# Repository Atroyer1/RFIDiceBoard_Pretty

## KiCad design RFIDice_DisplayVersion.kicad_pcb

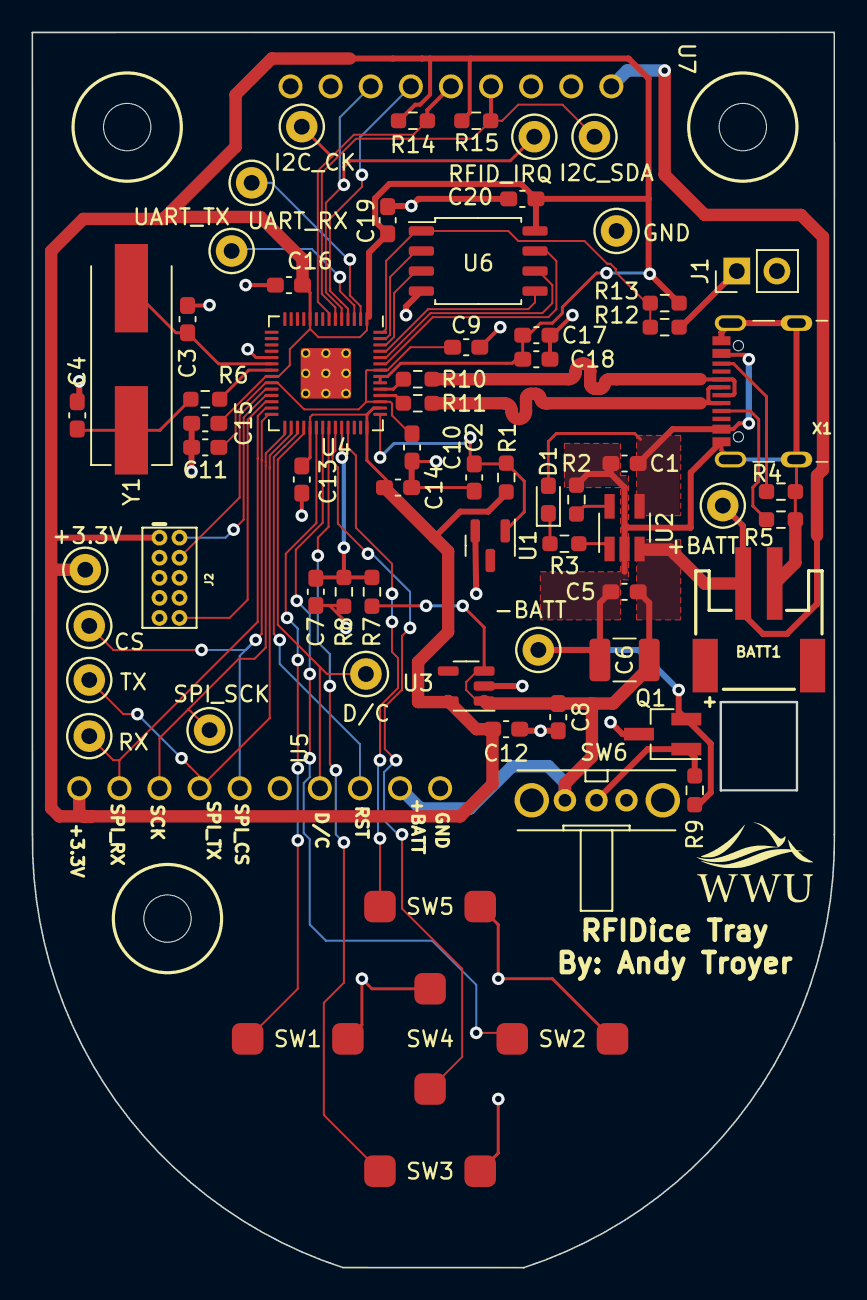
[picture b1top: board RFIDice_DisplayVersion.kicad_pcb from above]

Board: 2 copper layers, 50.8 x 78.3 mm, 73 parts (0 on the bottom side), 48 nets.

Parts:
 : LOGO
+3.3V: TestPoint; TestPoint_Keystone_5000-5004_Miniature
+BATT: TestPoint; TestPoint_Keystone_5000-5004_Miniature
-BATT: TestPoint; TestPoint_Keystone_5000-5004_Miniature
BATT1: Battery_Cell; JSTPH2
C1, C5: 4.7µF; C_0603_1608Metric_Pad1.08x0.95mm_HandSolder
C2, C7: 0.1µF; C_0603_1608Metric_Pad1.08x0.95mm_HandSolder
C3, C4: 27pF; C_0603_1608Metric_Pad1.08x0.95mm_HandSolder
C6: 22mF; C_1210_3225Metric_Pad1.33x2.70mm_HandSolder
C8, C12: 10µF; C_0603_1608Metric_Pad1.08x0.95mm_HandSolder
C9, C11, C13, C14, C15, C16, C17, C18, C19, C20: 100nF; C_0603_1608Metric_Pad1.08x0.95mm_HandSolder
C10: 1µF; C_0603_1608Metric_Pad1.08x0.95mm_HandSolder
CS: TestPoint; TestPoint_Keystone_5000-5004_Miniature
D1: LED; LED_0603_1608Metric_Pad1.05x0.95mm_HandSolder
D/C: TestPoint; TestPoint_Keystone_5000-5004_Miniature
GND: TestPoint; TestPoint_Keystone_5000-5004_Miniature
I2C_CK, I2C_SDA: TestPoint; TestPoint_Keystone_5000-5004_Miniature
J1: Conn_01x02; PinHeader_1x02_P2.54mm_Vertical
J2: CORTEX_JTAG_DEBUG_MINIMUM_PTH; 2X5-PTH-1.27MM
Q1: Q_NMOS_DGS; SOT-23_Handsoldering
R1, R6, R12: 1kΩ; R_0603_1608Metric_Pad0.98x0.95mm_HandSolder
R2, R7, R8, R14, R15: 10kΩ; R_0603_1608Metric_Pad0.98x0.95mm_HandSolder
R3: 470Ω; R_0603_1608Metric_Pad0.98x0.95mm_HandSolder
R4, R5: 5.1kΩ; R_0603_1608Metric_Pad0.98x0.95mm_HandSolder
R9: 470kΩ; R_0603_1608Metric_Pad0.98x0.95mm_HandSolder
R10, R11: 27Ω; R_0603_1608Metric_Pad0.98x0.95mm_HandSolder
R13: DNF; R_0603_1608Metric_Pad0.98x0.95mm_HandSolder
RFID_IRQ: TestPoint; TestPoint_Keystone_5000-5004_Miniature
RX: TestPoint; TestPoint_Keystone_5000-5004_Miniature
SPI_SCK: TestPoint; TestPoint_Keystone_5000-5004_Miniature
SW1, SW2, SW3, SW4, SW5: SW_Push; EVP-ASDC1A_Tactile_PushButton
SW6: OS102011MA1Q
TX: TestPoint; TestPoint_Keystone_5000-5004_Miniature
U1: LM4040DBZ-3; SOT-23
U2: MCP73831T-2ACI/OT; SOT-23-5_HandSoldering
U3: MIC5219-3.3YM5; SOT-23-5
U4: RP2040; RP2040-QFN-56
U5: Display; ThroughHoldDisplayMount
U6: W25Q128JVS; SOIC-8_5.23x5.23mm_P1.27mm
U7: PN532; ThroughHolePN532BrkOutBoardMount
U$6, U$6#2, U$6#3: MOUNTINGHOLE_3.0
UART_RX: TestPoint; TestPoint_Keystone_5000-5004_Miniature
UART_TX: TestPoint; TestPoint_Keystone_5000-5004_Miniature
X1: USB_C; USB_C_CUSB31-CFM2AX-01-X_copy
Y1: ABLS-12.000MHZ-B4-T; Crystal_SMD_HC49-US

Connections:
+1V1: C9.1, C10.1, C11.1, U4.23 (DVDD), U4.45 (VREG_VOUT), U4.50 (DVDD)
+3V3: +3.3V.1, C12.1, C13.1, C14.1, C15.1, C16.1, C17.1, C18.1, C19.1, C20.1, J2.1 (VCC), R1.1, R13.1, R14.2, R15.2, U3.5 (OUT), U4.1 (IOVDD), U4.10 (IOVDD), U4.22 (IOVDD), U4.33 (IOVDD), U4.42 (IOVDD), U4.44 (VREG_IN), U4.48 (USB_VDD), U4.49 (IOVDD), U5.1 (Lite), U6.8 (VCC)
+5V: C1.1, D1.2 (A), U2.4 (VDD), X1.A4B9 (VBUS), X1.B4A9 (VBUS)
+BATT: +BATT.1, BATT1.1 (+), C5.1, C6.1, C8.1, R7.1, SW6.1, U2.3 (VBAT), U3.1 (IN), U3.3 (EN), U5.9 (VCC), U7.1 (3.3V)
-BATT: -BATT.1, BATT1.2 (-), C1.2, C5.2, C6.2, Q1.3 (S), R2.2, R4.1, R5.1, R9.2, U2.2 (VSS), X1.A1B12 (GND), X1.B1A12 (GND), X1.M1, X1.M2, X1.M3, X1.M4
/2USB_D+: R10.1, U4.47 (USB_DP)
/2USB_D-: R11.1, U4.46 (USB_DM)
/ADC_VRef: C2.1, R1.2, U1.1 (K), U4.43 (ADC_AVDD)
/BTN1: SW1.1, U4.34 (GPIO22)
/BTN2: SW2.1, U4.35 (GPIO23)
/BTN3: SW3.1, U4.36 (GPIO24)
/BTN4: SW4.1, U4.37 (GPIO25)
/BTN5: SW5.1, U4.39 (GPIO27_ADC1)
/DISP_DATA/COMMAND: D/C.1, U4.32 (GPIO21), U5.7 (D/C)
/DISP_RST: U4.31 (GPIO20), U5.8 (Reset)
/HALF_BATT_REF: C7.1, R7.2, R8.1, U4.38 (GPIO26_ADC0)
/I2C0_SCL: I2C_CK.1, R14.1, U4.7 (GPIO5), U7.5 (SSEL/SCL/RX)
/I2C0_SDA: I2C_SDA.1, R15.1, U4.6 (GPIO4), U7.4 (MOSI/SDA/TX)
/PN532_IRQ: RFID_IRQ.1, U4.5 (GPIO3), U7.7 (IRQ)
/PN532_RSTOUT_N: U4.4 (GPIO2), U7.6 (RSTOUT_N)
/QSPI_SCLK: U4.52 (QSPI_SCLK), U6.6 (CLK)
/QSPI_SS: R12.2, R13.2, U4.56 (QSPI_SS), U6.1 (~CS)
/QSPL_SD0: U4.53 (QSPI_SD0), U6.5 (DI(IO0))
/QSPL_SD1: U4.55 (QSPI_SD1), U6.2 (DO(IO1))
/QSPL_SD2: U4.54 (QSPI_SD2), U6.3 (IO2)
/QSPL_SD3: U4.51 (QSPI_SD3), U6.7 (IO3)
/SPI_CS: CS.1, U4.28 (GPIO17), U5.5 (TFT_CS)
/SPI_RX: RX.1, U4.27 (GPIO16), U5.2 (MISO)
/SPI_SCK: SPI_SCK.1, U4.29 (GPIO18), U5.3 (SCK)
/SPI_TX: TX.1, U4.30 (GPIO19), U5.4 (MOSI)
/SWCLK: J2.4 (SWDCLK), U4.24 (SWCLK)
/SWD: J2.2 (SWDIO), U4.25 (SWD)
/UART0_RX: U4.2 (GPIO0), UART_RX.1
/UART0_TX: U4.3 (GPIO1), UART_TX.1
/USB_D+: R10.2, X1.A6 (D+), X1.B6 (D+)
/USB_D-: R11.2, X1.A7 (D-), X1.B7 (D-)
/XIN: C3.2, U4.20 (XIN), Y1.2
/XOUT: R6.2, U4.21 (XOUT)
/~RESET: J2.10 (~RESET), U4.26 (RUN)
/~USB_BOOT: J1.1, R12.1
GND: C2.2, C3.1, C4.1, C7.2, C8.2, C9.2, C10.2, C11.2, C12.2, C13.2, C14.2, C15.2, C16.2, C17.2, C18.2, C19.2, C20.2, GND.1, J1.2, J2.3 (GND), J2.5 (GND), J2.9 (GND), Q1.1 (D), R8.2, SW1.2, SW2.2, SW3.2, SW4.2, SW5.2, U1.2 (A), U3.2 (GND), U4.19 (TESTEN), U4.57 (GND), U5.10 (GND), U6.4 (GND), U7.8 (GND)
unnamed: C4.2, R6.1, Y1.1
unnamed: D1.1 (K), R3.1
unnamed: Q1.2 (G), R9.1, SW6.2
unnamed: R2.1, U2.5 (PROG)
unnamed: R3.2, U2.1 (STAT)
unnamed: R4.2, X1.B5 (CC2)
unnamed: R5.2, X1.A5 (CC1)

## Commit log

2023-02-06 InitialKicadCommit
2023-02-10 StartedPCBWork
2023-02-10 Last commit had nothing in it
2023-02-14 Gonna go back and change start from power instead
2023-02-15 Maybe probably finished
2023-02-15 Commented on PCB
2023-02-15 Fixed cutout section
2023-02-17 Probably final commit
